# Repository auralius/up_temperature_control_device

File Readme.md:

This is a repository for the Universitas Pertamina's temperature control device.

Visit this page for some projects that can be implemented to the device:   

https://bit.ly/TemperatureControlDevice  

Features:
- Low cost.
- Open hardware and software, you can make your own.
- Excellent linearity at steady state condition when the temperature is below 120 degress of Celcius.
- Two heaters with two temperature sensors.
- Each heater can be heated to about 140 degrees of Celcius.
- The device is designed such that only the power resistors that become hot. The driving transistors barely become hot.

The software that is used is MATLAB Simulink with the Arduino support package. It is also possible to use LabVIEW with Linx libraries for the Arduino.

You might also want to look into the Arduino TCLab from Birgham Young University, where we mainly get our inspiration from: http://apmonitor.com/pdc/index.php/Main/ArduinoTemperatureControl

There is also one from RMIT, Australia: https://journals.sagepub.com/doi/10.1177/0020720919852784

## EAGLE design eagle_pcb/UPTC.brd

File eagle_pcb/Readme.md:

Eagle version: 9.5.2 Education

There is a ZIP file containing the GERBER files which have been successfully sent for productions.

The schematic:

The PCB:

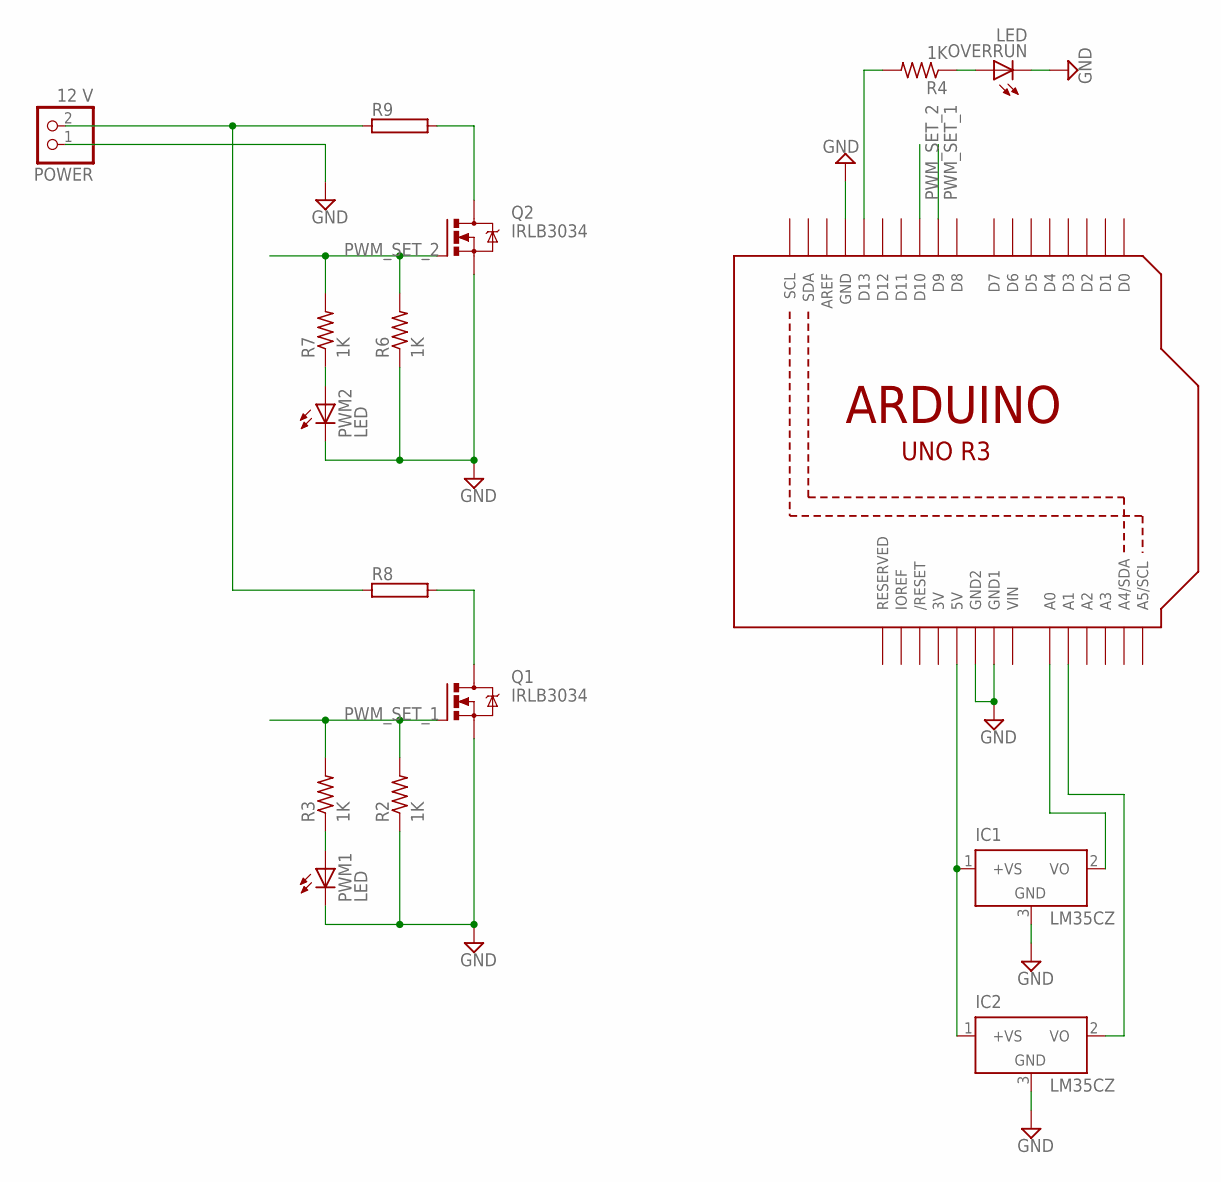
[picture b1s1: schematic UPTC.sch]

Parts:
IC1, IC2: LM35CZ; TO92
OVERRUN: LED; LED5MM
POWER: 12 V; 1X02
PWM1, PWM2: LED; LED5MM
Q1, Q2: IRLB3034; TO220BV
R2, R3, R4, R6, R7: 1K; 0207/10
R8, R9: RAC05; AC05
U2: ARDUINOR3-BPLACE

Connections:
3V: U2.3V
GND: IC1.3 (GND), IC2.3 (GND), OVERRUN.K (C), POWER.1, PWM1.K (C), PWM2.K (C), Q1.S, Q2.S, R2.1, R6.1, U2.GND, U2.GND1, U2.GND2
unnamed: Q1.D, R8.2
unnamed: IC1.2 (VO), U2.A0
unnamed: R4.2, U2.D13
unnamed: PWM1.A, R3.1
unnamed: OVERRUN.A, R4.1
unnamed: IC2.2 (VO), U2.A1
unnamed: Q2.D, R9.2
unnamed: PWM2.A, R7.1
unnamed: POWER.2, R8.1, R9.1
PWM_SET_1: Q1.G, R2.2, R3.2, U2.D9
PWM_SET_2: Q2.G, R6.2, R7.2, U2.D10
VCC: IC1.1 (+VS), IC2.1 (+VS), U2.5V
VIN: U2.VIN

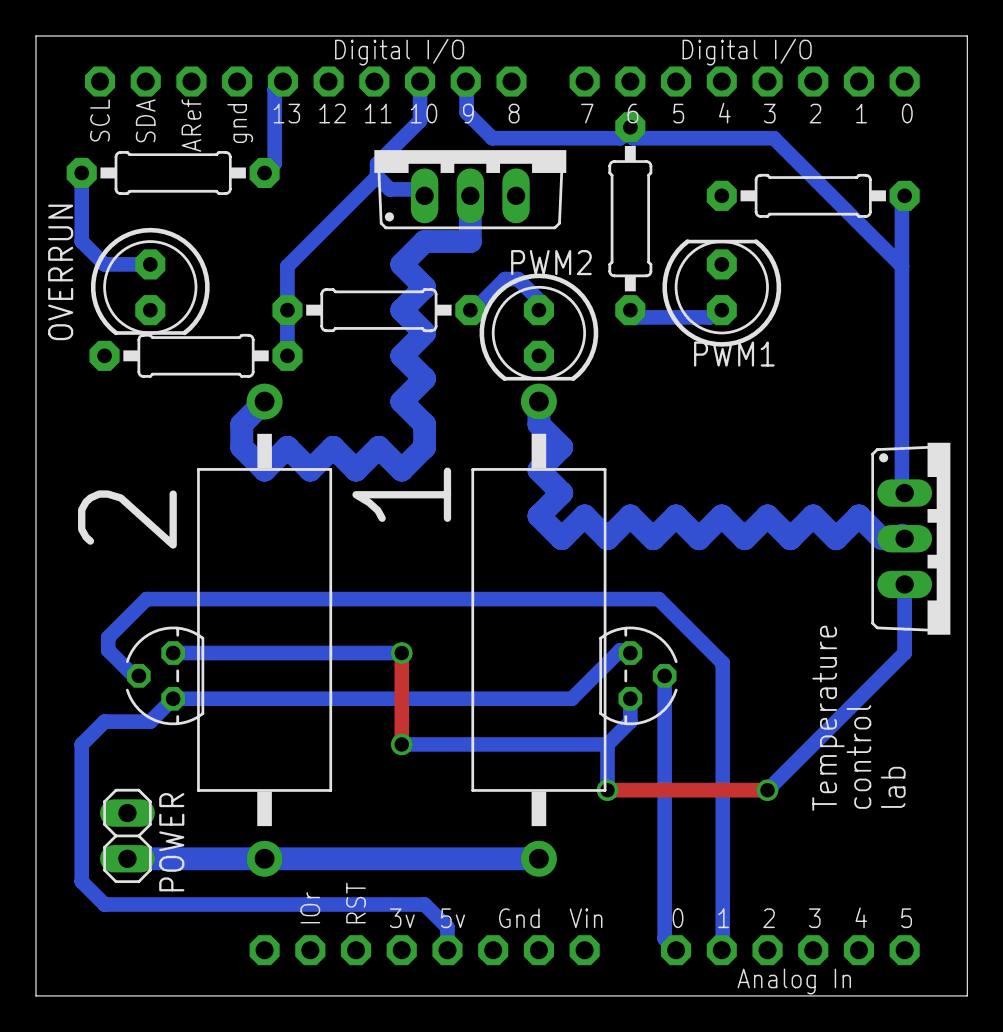
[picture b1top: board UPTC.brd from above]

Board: 2 copper layers, 51.7 x 53.3 mm, 16 parts (0 on the bottom side), 13 nets.

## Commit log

2020-06-16 Hariott model and its optimization.
2020-06-16 Presentation material on modelling a thermal system as a mass-spring-damper system.
2020-06-17 Updated the ppt: SPODT with optimization process
2020-06-28 updated the SOPDT Optimization.pptx
2020-06-28 Smith Predictor
2020-06-28 updated the LabVIEW files
2020-06-28 added the smith predictor ppt file
2020-07-29 Set theme jekyll-theme-minimal
2020-07-29 Energy balance model
2020-07-29 Added a PPT file on the topic of energy balance model
2020-08-02 Hariott Model
2020-08-02 Update the presentation files
2020-08-02 Updated the Smith Predictor
2022-04-28 A new start.
2022-04-28 Add a new paper in references.
2022-04-30 General delay implementation
2022-04-30 Restrucutre the folder following the document.
2022-05-01 Add the energy balance model topic.
